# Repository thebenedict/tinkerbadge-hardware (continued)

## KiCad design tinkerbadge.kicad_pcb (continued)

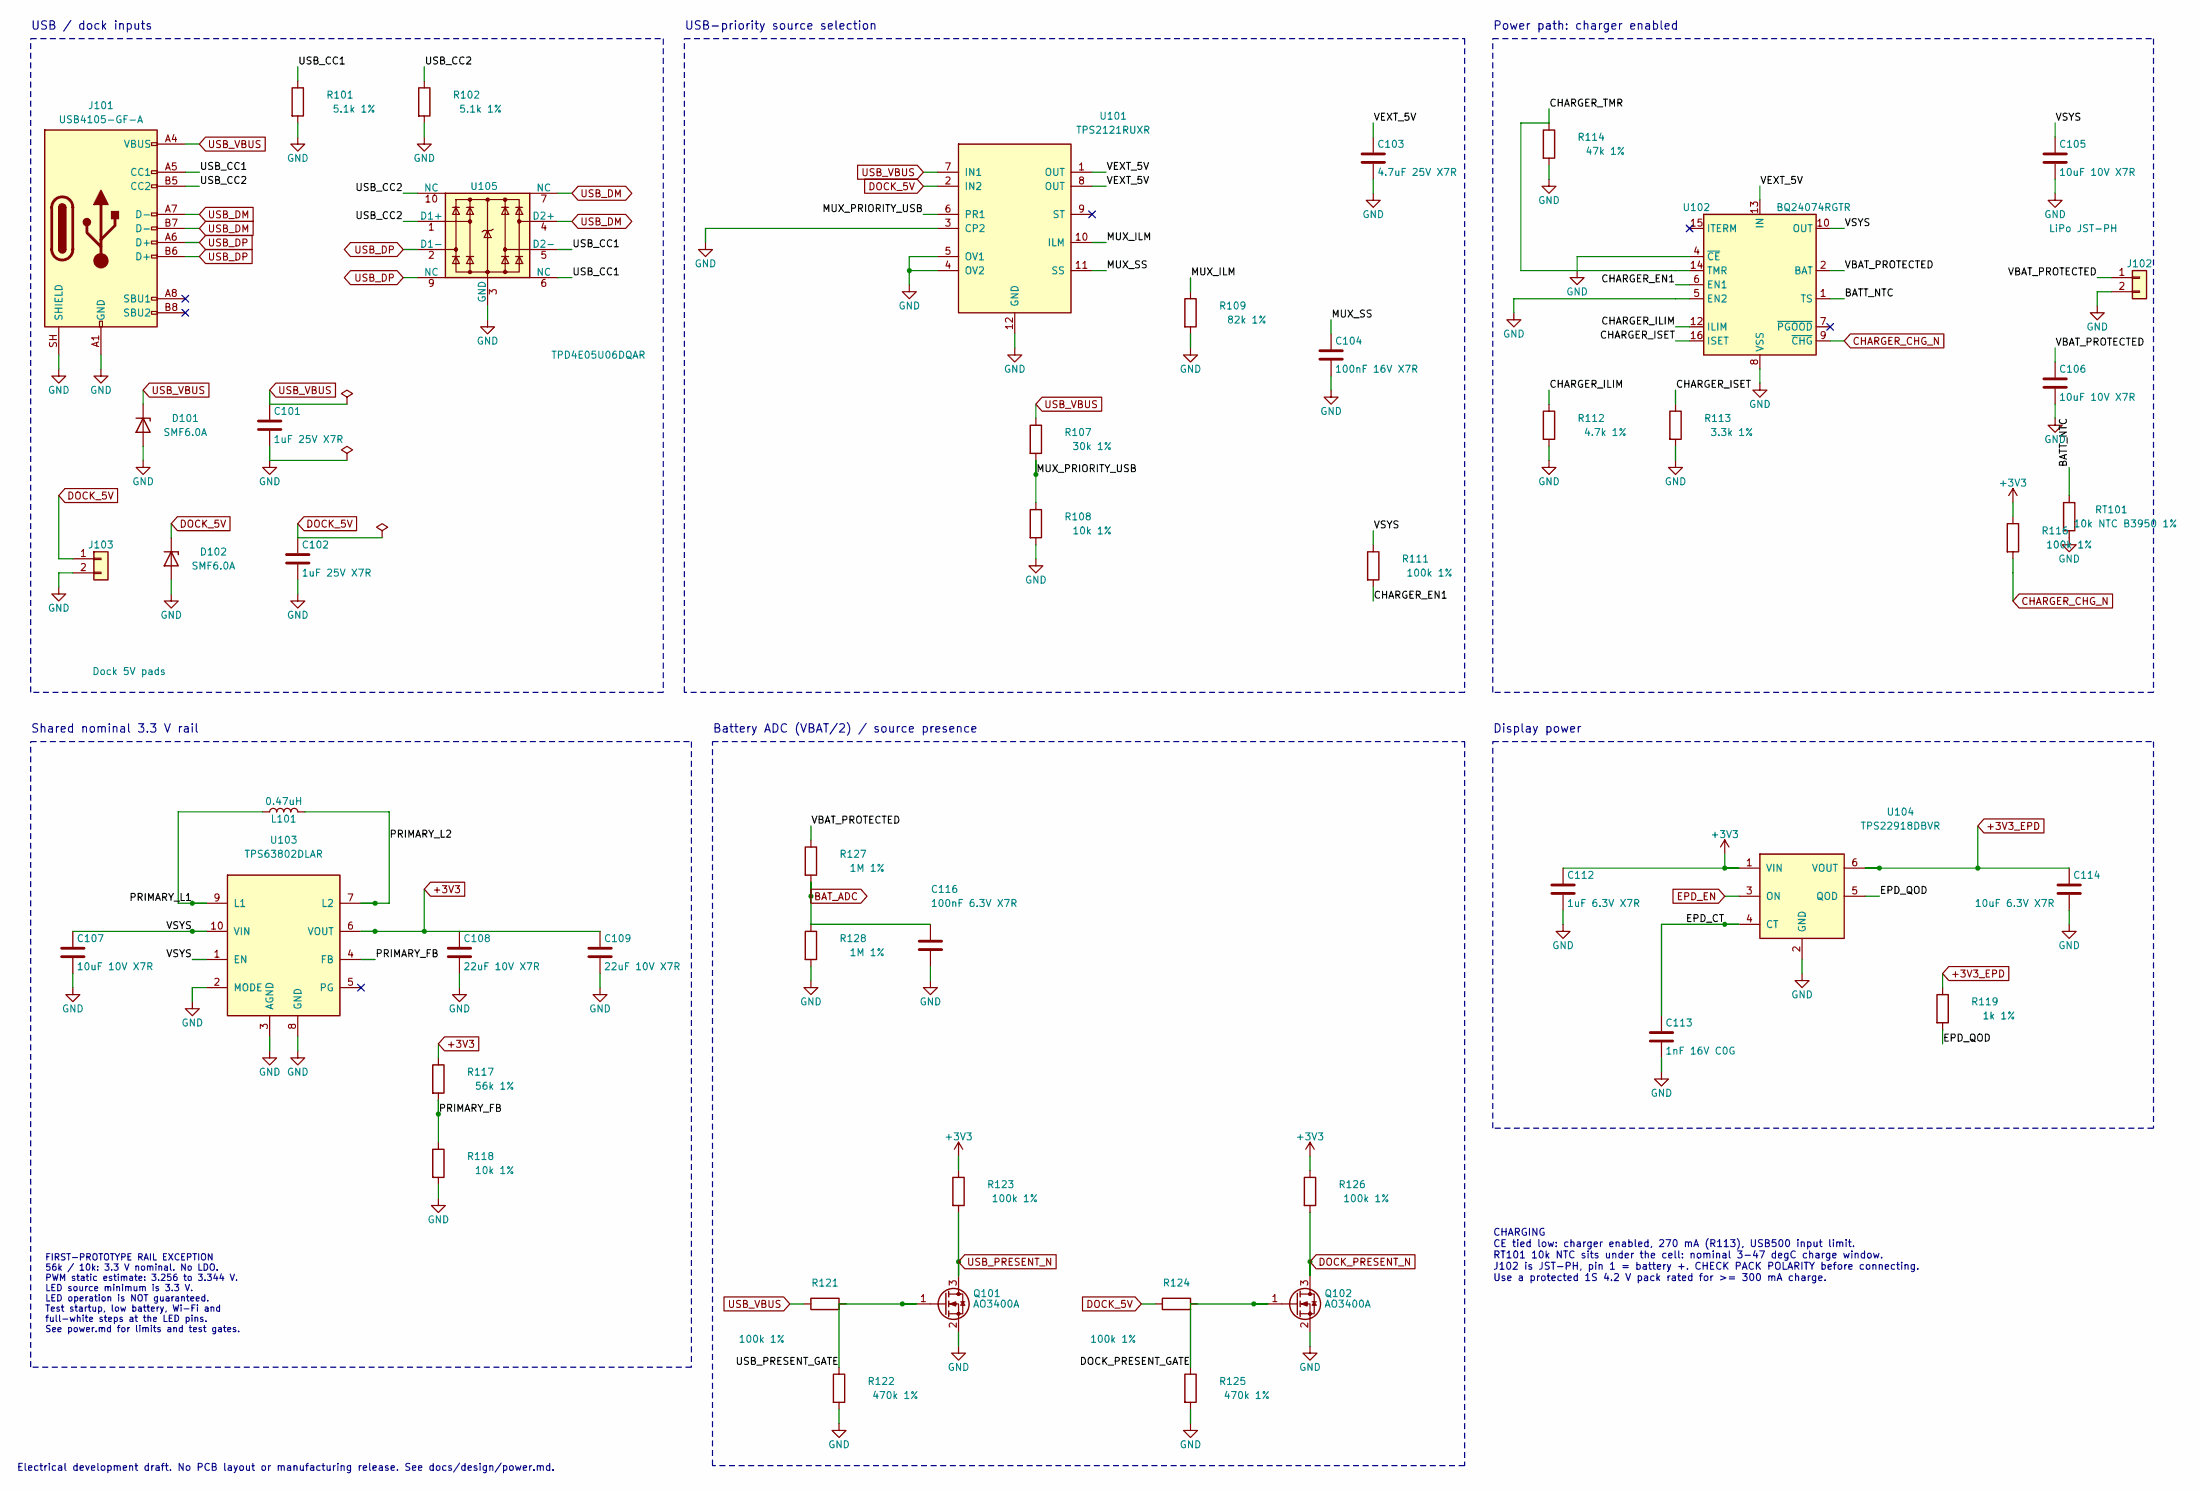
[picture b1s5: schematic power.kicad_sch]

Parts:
C101, C102: 1uF 25V X7R; C_0805_2012Metric; MPN CL21B105KBFNNNE; LCSC C28323
C103: 4.7uF 25V X7R; C_1206_3216Metric; MPN 1206B475K500NT; LCSC C29823
C104: 100nF 16V X7R; C_0603_1608Metric; MPN CC0603KRX7R9BB104; LCSC C14663
C105, C106, C107: 10uF 10V X7R; C_0805_2012Metric; MPN CL21A106KAYNNNE; LCSC C15850
C108, C109: 22uF 10V X7R; C_1210_3225Metric; MPN CL32B226KAJNNNE; LCSC C309062
C112: 1uF 6.3V X7R; C_0805_2012Metric; MPN CL21B105KBFNNNE; LCSC C28323
C113: 1nF 16V C0G; C_0603_1608Metric; MPN CL10B102KB8NNNC; LCSC C1588
C114: 10uF 6.3V X7R; C_0805_2012Metric; MPN CL21A106KAYNNNE; LCSC C15850
C116: 100nF 6.3V X7R; C_0603_1608Metric; MPN CC0603KRX7R9BB104; LCSC C14663
D101, D102: SMF6.0A; MPN SMF6.0A; LCSC C19077499
J101: USB4105-GF-A; USB4105-GF-A_ProjectShells; MPN USB4105-GF-A; LCSC C3020560
J102: LiPo JST-PH; JST_PH_S2B-PH-K_1x02_P2.00mm_Horizontal; MPN S2B-PH-K-S(LF)(SN); LCSC C173752
J103: Dock 5V pads; Dock_Pads_2x_4x6mm; MPN PCB pads only: no fitted component
L101: 0.47uH; L_Changjiang_FNR4020S; MPN SWPA4020SR47NT; LCSC C98415
Q101, Q102: AO3400A; SOT-23; MPN AO3400A; LCSC C20917
R101, R102: 5.1k 1%; R_0603_1608Metric; MPN 0603WAF5101T5E; LCSC C23186
R107: 30k 1%; R_0603_1608Metric; MPN 0603WAF3002T5E; LCSC C22984
R108, R118: 10k 1%; R_0603_1608Metric; MPN 0603WAF1002T5E; LCSC C25804
R109: 82k 1%; R_0603_1608Metric; MPN 0603WAF8202T5E; LCSC C23254
R111, R116, R121, R123, R124, R126: 100k 1%; R_0603_1608Metric; MPN 0603WAF1003T5E; LCSC C25803
R112: 4.7k 1%; R_0603_1608Metric; MPN 0603WAF4701T5E; LCSC C23162
R113: 3.3k 1%; R_0603_1608Metric; MPN 0603WAF3301T5E; LCSC C22978
R114: 47k 1%; R_0603_1608Metric; MPN 0603WAF4702T5E; LCSC C25819
R117: 56k 1%; R_0603_1608Metric; MPN 0603WAF5602T5E; LCSC C23206
R119: 1k 1%; R_0603_1608Metric; MPN 0603WAF1001T5E; LCSC C21190
R122, R125: 470k 1%; R_0603_1608Metric; MPN 0603WAF4703T5E; LCSC C23178
R127, R128: 1M 1%; R_0603_1608Metric; MPN 0603WAF1004T5E; LCSC C22935
RT101: 10k NTC B3950 1%; R_0603_1608Metric; MPN KNTC0603/10KF3950; LCSC C2892547
U101: TPS2121RUXR; TPS2121RUXR_Reviewed; MPN TPS2121RUXR; LCSC C485916
U102: BQ24074RGTR; BQ24074RGTR_Reviewed; MPN BQ24074RGTR; LCSC C54313
U103: TPS63802DLAR; TPS63802_DLA0010A_Reviewed; MPN TPS63802DLAR; LCSC C2845237
U104: TPS22918DBVR; SOT-23-6; MPN TPS22918DBVR; LCSC C131941
U105: TPD4E05U06DQAR; USON-10_2.5x1.0mm_P0.5mm; MPN TPD4E05U06DQAR; LCSC C138714

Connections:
+3V3: C108.1, C109.1, C112.1, R116.1, R117.1, R123.1, R126.1, U103.6 (VOUT), U104.1 (VIN); also elsewhere on the board
+3V3_EPD: C114.1, R119.1, U104.6 (VOUT); also elsewhere on the board
/01 POWER + CHARGING/BATT_NTC: RT101.1, U102.1 (TS)
/01 POWER + CHARGING/CHARGER_EN1: R111.2, U102.6 (EN1)
/01 POWER + CHARGING/CHARGER_ILIM: R112.1, U102.12 (ILIM)
/01 POWER + CHARGING/CHARGER_ISET: R113.1, U102.16 (ISET)
/01 POWER + CHARGING/DOCK_PRESENT_GATE: Q102.1 (G), R124.2, R125.1
/01 POWER + CHARGING/EPD_CT: C113.1, U104.4 (CT)
/01 POWER + CHARGING/EPD_QOD: R119.2, U104.5 (QOD)
/01 POWER + CHARGING/MUX_ILM: R109.1, U101.10 (ILM)
/01 POWER + CHARGING/MUX_PRIORITY_USB: R107.2, R108.1, U101.6 (PR1)
/01 POWER + CHARGING/MUX_SS: C104.1, U101.11 (SS)
/01 POWER + CHARGING/PRIMARY_FB: R117.2, R118.1, U103.4 (FB)
/01 POWER + CHARGING/PRIMARY_L1: L101.1, U103.9 (L1)
/01 POWER + CHARGING/PRIMARY_L2: L101.2, U103.7 (L2)
/01 POWER + CHARGING/USB_CC1: J101.A5 (CC1), R101.1, U105.5 (D2-), U105.6 (NC)
/01 POWER + CHARGING/USB_CC2: J101.B5 (CC2), R102.1, U105.1 (D1+), U105.10 (NC)
/01 POWER + CHARGING/USB_PRESENT_GATE: Q101.1 (G), R121.2, R122.1
/01 POWER + CHARGING/VBAT_PROTECTED: C106.1, J102.1, R127.1, U102.2 (BAT), U102.3 (BAT)
/01 POWER + CHARGING/VEXT_5V: C103.1, U101.1 (OUT), U101.8 (OUT), U102.13 (IN)
/01 POWER + CHARGING/VSYS: C105.1, C107.1, R111.1, U102.10 (OUT), U102.11 (OUT), U103.1 (EN), U103.10 (VIN)
BAT_ADC: C116.1, R127.2, R128.1; also elsewhere on the board
CHARGER_CHG_N: R116.2, U102.9 (~CHG); also elsewhere on the board
DOCK_PRESENT_N: Q102.3 (D), R126.2; also elsewhere on the board
EPD_EN: U104.3 (ON); also elsewhere on the board
USB_DM: J101.A7 (D-), J101.B7 (D-), U105.4 (D2+), U105.7 (NC); also elsewhere on the board
USB_DP: J101.A6 (D+), J101.B6 (D+), U105.2 (D1-), U105.9 (NC); also elsewhere on the board
USB_PRESENT_N: Q101.3 (D), R123.2; also elsewhere on the board

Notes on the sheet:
USB / dock inputs
USB-priority source selection
Power path: charger enabled
Battery ADC (VBAT/2) / source presence
Display power
Electrical development draft. No PCB layout or manufacturing release. See docs/design/power.md.
CHARGING CE tied low: charger enabled, 270 mA (R113), USB500 input limit. RT101 10k NTC sits under the cell: nominal 3-47 degC charge window. J102 is JST-PH, pin 1 = battery +. CHECK PACK POLARITY before connecting. Use a protected 1S 4.2 V pack rated for >= 300 mA charge.
Shared nominal 3.3 V rail
FIRST-PROTOTYPE RAIL EXCEPTION 56k / 10k: 3.3 V nominal. No LDO. PWM static estimate: 3.256 to 3.344 V. LED source minimum is 3.3 V. LED operation is NOT guaranteed. Test startup, low battery, Wi-Fi and full-white steps at the LED pins. See power.md for limits and test gates.

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
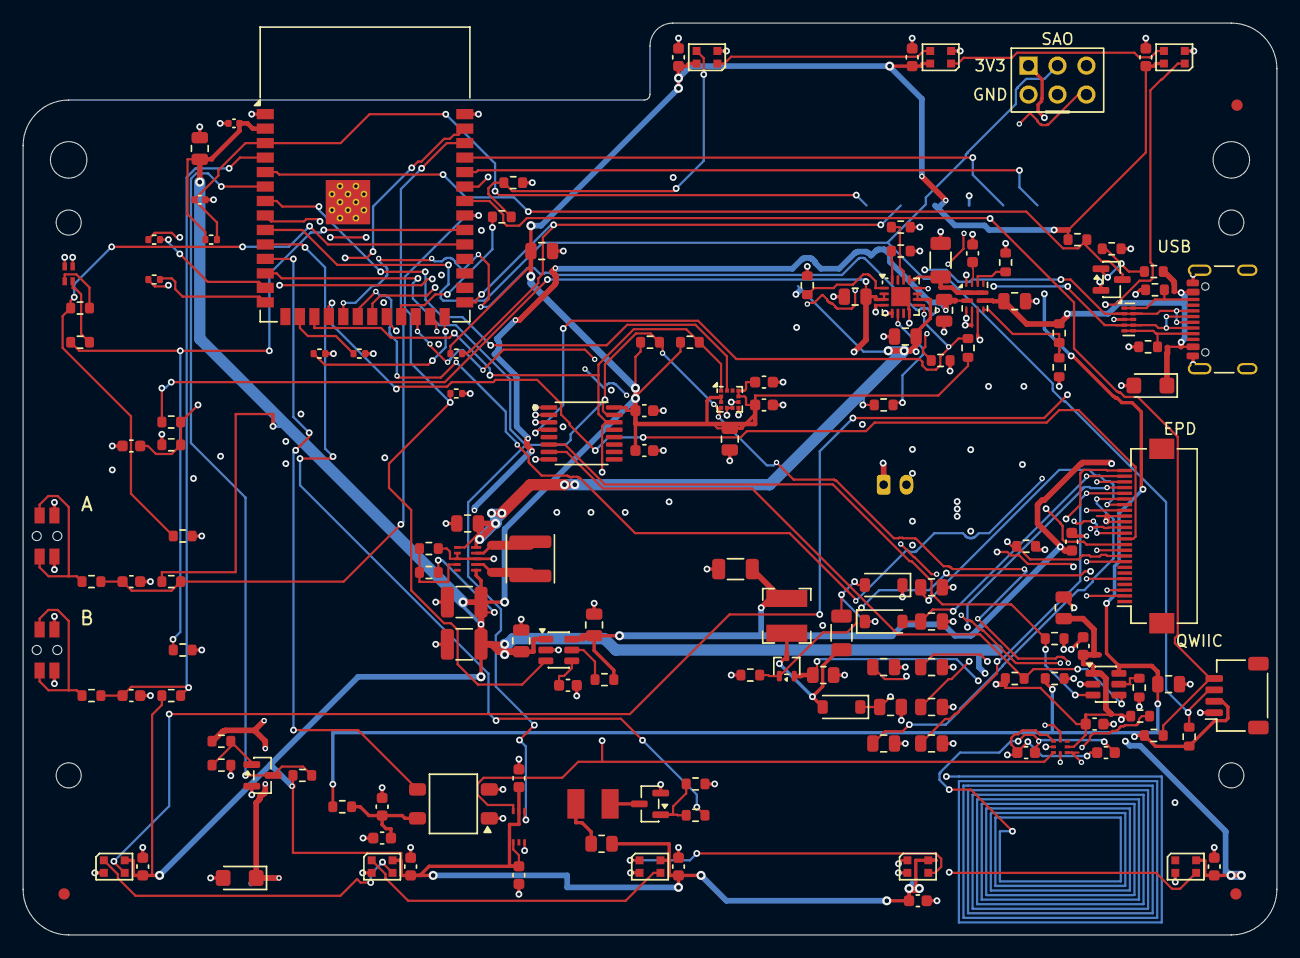
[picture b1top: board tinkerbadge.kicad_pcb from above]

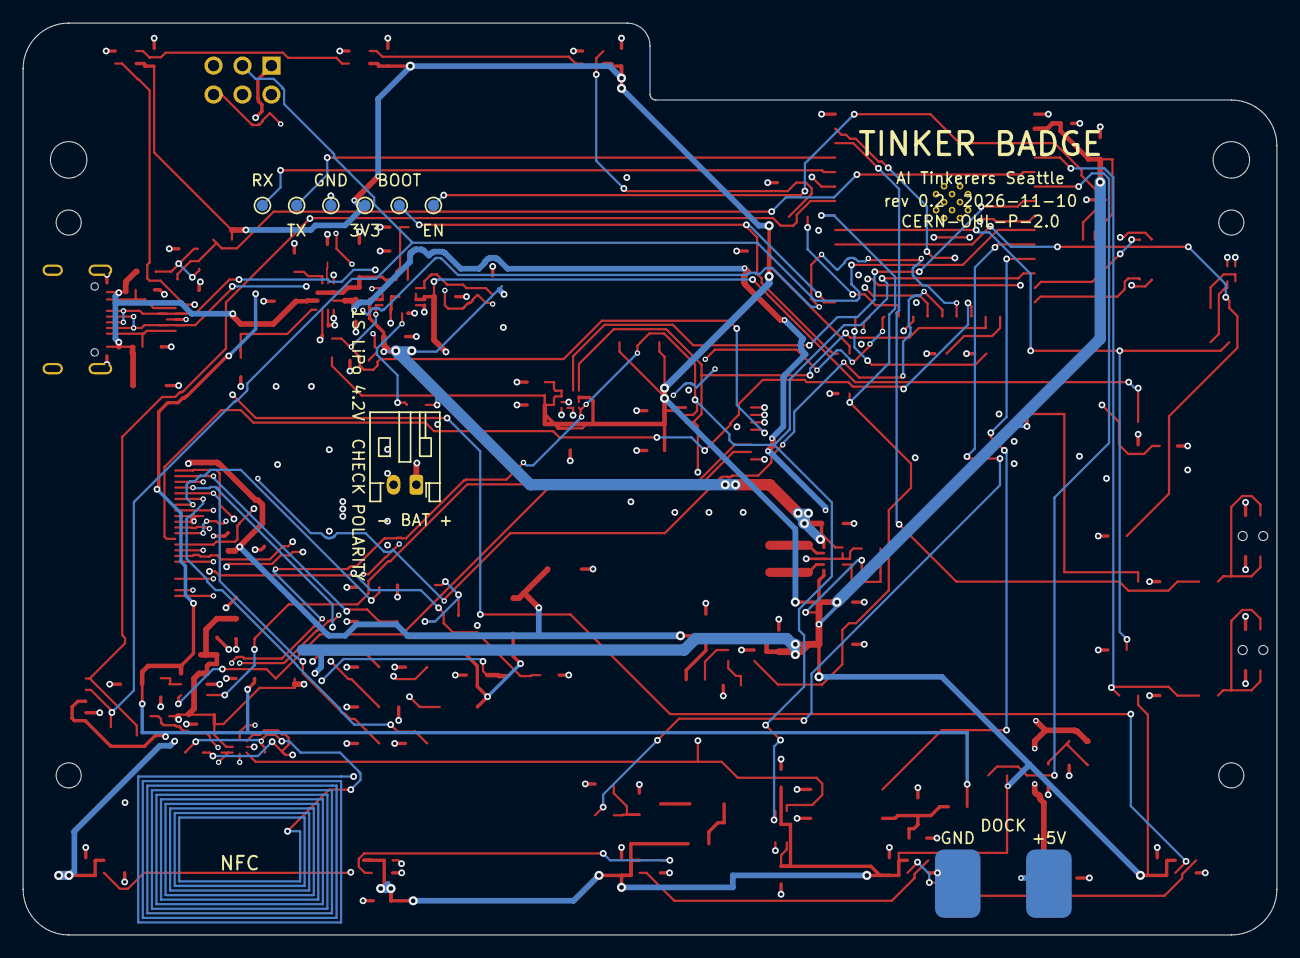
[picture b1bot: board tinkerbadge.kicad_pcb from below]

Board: 4 copper layers, 110.0 x 80.0 mm, 167 parts (10 on the bottom side), 95 nets.

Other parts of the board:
FID1, FID2, FID3: Fiducial; Fiducial_1mm_Mask2mm
H1, H2, H3, H4: PROVISIONAL; MountingHole_2.2mm_M2
H5, H6: REVIEW ENVELOPE ONLY; Review_Cord_Hole_3p2
MECH_BATTERY: REVIEW ONLY; Review_Battery_Allowance
MECH_PANEL: REVIEW ENVELOPE ONLY; Review_Panel_Raised_4p5

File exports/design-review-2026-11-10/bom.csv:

"Reference","Value","Footprint","MPN","Qty","DNP"
"C101,C102","1uF 25V X7R","Capacitor_SMD:C_0805_2012Metric","CL21B105KBFNNNE","2",""
"C103","4.7uF 25V X7R","Capacitor_SMD:C_1206_3216Metric","1206B475K500NT","1",""
"C104","100nF 16V X7R","Capacitor_SMD:C_0603_1608Metric","CC0603KRX7R9BB104","1",""
"C105-C107","10uF 10V X7R","Capacitor_SMD:C_0805_2012Metric","CL21A106KAYNNNE","3",""
"C108,C109","22uF 10V X7R","Capacitor_SMD:C_1210_3225Metric","CL32B226KAJNNNE","2",""
"C112","1uF 6.3V X7R","Capacitor_SMD:C_0805_2012Metric","CL21B105KBFNNNE","1",""
"C113","1nF 16V C0G","Capacitor_SMD:C_0603_1608Metric","CL10B102KB8NNNC","1",""
"C114","10uF 6.3V X7R","Capacitor_SMD:C_0805_2012Metric","CL21A106KAYNNNE","1",""
"C116","100nF 6.3V X7R","Capacitor_SMD:C_0603_1608Metric","CC0603KRX7R9BB104","1",""
"C201","22uF 10V X5R","Capacitor_SMD:C_0805_2012Metric","CL21A226MAQNNNE","1",""
"C202","100nF 16V X7R","Capacitor_SMD:C_0402_1005Metric","CL05B104KO5NNNC","1",""
"C203","1uF 10V X7R","Capacitor_SMD:C_0402_1005Metric","CL05A105KA5NQNC","1",""
"C301,C302","4.7u / 50V","Capacitor_SMD:C_1206_3216Metric","1206B475K500NT","2",""
"C303,C401-C408,C411,C412,C501-C504,C506,C510,C514","100n / 10V","Capacitor_SMD:C_0603_1608Metric","CC0603KRX7R9BB104","18",""
"C304","1u / 10V","Capacitor_SMD:C_0805_2012Metric","CL21B105KBFNNNE","1",""
"C305,C311","1u / 25V","Capacitor_SMD:C_0805_2012Metric","CL21B105KBFNNNE","2",""
"C306-C310","1u / 50V","Capacitor_SMD:C_0805_2012Metric","CL21B105KBFNNNE","5",""
"C409","22u / 10V","Capacitor_SMD:C_0805_2012Metric","CL21A226MAQNNNE","1",""
"C505,C512,C513","10u / 10V","Capacitor_SMD:C_0805_2012Metric","CL21A106KAYNNNE","3",""
"C507","27p C0G (tune)","Capacitor_SMD:C_0603_1608Metric","CC0603JRNPO9BN270","1",""
"C509","4.7u / 10V","Capacitor_SMD:C_0603_1608Metric","CL10A475KO8NNNC","1",""
"C511,C515","1u / 10V","Capacitor_SMD:C_0603_1608Metric","CL10A105KB8NNNC","2",""
"D101,D102","SMF6.0A","Tinkerbadge:SMF6.0A","SMF6.0A","2",""
"D301-D303","MBR0530T1G","Diode_SMD:D_SOD-123","MBR0530T1G","3",""
"D401-D408","WS2812C-2020-V6","Tinkerbadge:WS2812C-2020-V6_Reviewed","WS2812C-2020-V6","8",""
"D409","HSMF-C165","Tinkerbadge:HSMF-C165","HSMF-C165","1",""
"D501","IR67-21C/TR8","Tinkerbadge:IR67-21C_TR8","IR67-21C/TR8","1",""
"J101","USB4105-GF-A","Tinkerbadge:USB4105-GF-A_ProjectShells","USB4105-GF-A","1",""
"J102","LiPo JST-PH","Connector_JST:JST_PH_S2B-PH-K_1x02_P2.00mm_Horizontal","S2B-PH-K-S(LF)(SN)","1",""
"J301","ED037TC1_FPC","Connector_FFC-FPC:Hirose_FH12-24S-0.5SH_1x24-1MP_P0.50mm_Horizontal","FH12-24S-0.5SH(55)","1",""
"J501","SM04B-SRSS-TB(LF)(SN)","Tinkerbadge:JST_SH_SM04B_ProjectTabs","SM04B-SRSS-TB(LF)(SN)","1",""
"J502","SFH11-NBPC-D03-ST-BK","Tinkerbadge:SAO_Socket_2x03_Front","SFH11-NBPC-D03-ST-BK","1",""
"L101","0.47uH","Inductor_SMD:L_Changjiang_FNR4020S","SWPA4020SR47NT","1",""
"L301","68uH","Inductor_SMD:L_Bourns-SRN4018","SRN4018-680M","1",""
"Q101,Q102,Q501","AO3400A","Package_TO_SOT_SMD:SOT-23","AO3400A","3",""
"Q301","Si1308EDL-T1-GE3","Package_TO_SOT_SMD:SOT-323_SC-70","SI1308EDL-T1-GE3","1",""
"R101,R102","5.1k 1%","Resistor_SMD:R_0603_1608Metric","0603WAF5101T5E","2",""
"R107","30k 1%","Resistor_SMD:R_0603_1608Metric","0603WAF3002T5E","1",""
"R108,R118","10k 1%","Resistor_SMD:R_0603_1608Metric","0603WAF1002T5E","2",""
"R109","82k 1%","Resistor_SMD:R_0603_1608Metric","0603WAF8202T5E","1",""
"R111,R116,R121,R123,R124,R126","100k 1%","Resistor_SMD:R_0603_1608Metric","0603WAF1003T5E","6",""
"R112","4.7k 1%","Resistor_SMD:R_0603_1608Metric","0603WAF4701T5E","1",""
"R113","3.3k 1%","Resistor_SMD:R_0603_1608Metric","0603WAF3301T5E","1",""
"R114","47k 1%","Resistor_SMD:R_0603_1608Metric","0603WAF4702T5E","1",""
"R117","56k 1%","Resistor_SMD:R_0603_1608Metric","0603WAF5602T5E","1",""
"R119","1k 1%","Resistor_SMD:R_0603_1608Metric","0603WAF1001T5E","1",""
"R122,R125","470k 1%","Resistor_SMD:R_0603_1608Metric","0603WAF4703T5E","2",""
"R127,R128","1M 1%","Resistor_SMD:R_0603_1608Metric","0603WAF1004T5E","2",""
"R201-R204","10k 1%","Resistor_SMD:R_0402_1005Metric","0402WGF1002TCE","4",""
"R205,R206","22R 1%","Resistor_SMD:R_0402_1005Metric","0402WGF220JTCE","2",""
"R207","100k 1%","Resistor_SMD:R_0402_1005Metric","0402WGF1003TCE","1",""
"R301","0.47 / 0.25W","Resistor_SMD:R_0805_2012Metric","FBF05FT-R470-00L","1",""
"R302,R503","10k","Resistor_SMD:R_0603_1608Metric","0603WAF1002T5E","2",""
"R308,R402,R405,R406,R412,R414,R506,R509-R511","100k","Resistor_SMD:R_0603_1608Metric","0603WAF1003T5E","10",""
"R401,R411,R413","330","Resistor_SMD:R_0603_1608Metric","0603WAF3300T5E","3",""
"R403,R404","2.2k","Resistor_SMD:R_0603_1608Metric","0603WAF2201T5E","2",""
"R501,R502,R512,R513","4.7k","Resistor_SMD:R_0603_1608Metric","0603WAF4701T5E","4",""
"R504","100","Resistor_SMD:R_0805_2012Metric","0805W8F1000T5E","1",""
"R505,R507","100","Resistor_SMD:R_0603_1608Metric","0603WAF1000T5E","2",""
"R508","200k","Resistor_SMD:R_0603_1608Metric","0603WAF2003T5E","1",""
"RT101","10k NTC B3950 1%","Resistor_SMD:R_0603_1608Metric","KNTC0603/10KF3950","1",""
"SW401,SW402","SKSCLBE010","Tinkerbadge:SKSCLBE010","SKSCLBE010","2",""
"TP201","MCU_EN","TestPoint:TestPoint_Pad_D1.0mm","PCB pad only: no fitted component","1",""
"TP202","BOOT_N","TestPoint:TestPoint_Pad_D1.0mm","PCB pad only: no fitted component","1",""
"TP203","+3V3","TestPoint:TestPoint_Pad_D1.0mm","PCB pad only: no fitted component","1",""
"TP204","GND","TestPoint:TestPoint_Pad_D1.0mm","PCB pad only: no fitted component","1",""
"TP205","UART_TX","TestPoint:TestPoint_Pad_D1.0mm","PCB pad only: no fitted component","1",""
"TP206","UART_RX","TestPoint:TestPoint_Pad_D1.0mm","PCB pad only: no fitted component","1",""
"U101","TPS2121RUXR","Tinkerbadge:TPS2121RUXR_Reviewed","TPS2121RUXR","1",""
"U102","BQ24074RGTR","Tinkerbadge:BQ24074RGTR_Reviewed","BQ24074RGTR","1",""
"U103","TPS63802DLAR","Tinkerbadge:TPS63802_DLA0010A_Reviewed","TPS63802DLAR","1",""
"U104","TPS22918DBVR","Package_TO_SOT_SMD:SOT-23-6","TPS22918DBVR","1",""
"U105","TPD4E05U06DQAR","Package_SON:USON-10_2.5x1.0mm_P0.5mm","TPD4E05U06DQAR","1",""
"U201","ESP32-S3-WROOM-1-N16R8","RF_Module:ESP32-S3-WROOM-1","ESP32-S3-WROOM-1-N16R8","1",""
"U501","BH1730FVC","Tinkerbadge:BH1730FVC_WSOF6","BH1730FVC","1",""
"U502","LIS2DW12TR","Package_LGA:LGA-12_2x2mm_P0.5mm","LIS2DW12TR","1",""
"U503","NT3H2111W0FHKH","Tinkerbadge:NT3H2111W0FHKH_XQFN8","NT3H2111W0FHKH","1",""
"U504","IRM-H638T/TR2","Tinkerbadge:IRM-H638T_Reviewed","IRM-H638T/TR2","1",""
"U505","TPS2553DBVR","Package_TO_SOT_SMD:SOT-23-6","TPS2553DBVR","1",""
"U506","TCA9534PWR","Package_SO:TSSOP-16_4.4x5mm_P0.65mm","TCA9534PWR","1",""

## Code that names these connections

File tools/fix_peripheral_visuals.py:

#!/usr/bin/env python3
"""Targeted visual fixes after saved-sheet render review; native writes via MCP."""
import json,pathlib,time
from konnect_call import Client,unbox
root=pathlib.Path(__file__).resolve().parents[1];out=root/'.build/peripheral_cad';calls=[]
def add(sheet,name,**a):calls.append(dict(name=name,arguments=dict(schematic=str(root/(sheet+'.kicad_sch')),**a)))
def fields(sheet,r,x,y,rot=0):add(sheet,'edit_schematic_component',reference=r,field_placements={'Reference':dict(x=x,y=y,rotation=rot),'Value':dict(x=x,y=y+2.54,rotation=rot)})
def oldwire(sheet,a,b):add(sheet,'delete_schematic_wire',x1=a[0],y1=a[1],x2=b[0],y2=b[1])
def wires(sheet,points):add(sheet,'batch_add_wire',wires=[dict(x1=a[0],y1=a[1],x2=b[0],y2=b[1]) for a,b in zip(points,points[1:])])
def label(sheet,n,x,y,g=False,rot=0):add(sheet,'add_schematic_net_label',net=n,x=x,y=y,label_type='global_label' if g else 'net_label',rotation=rot,shape='bidirectional')
def dellabel(sheet,n,x,y):add(sheet,'delete_schematic_net_label',net=n,x=x,y=y)
for r,x in [('SW401',195.58),('SW402',297.18)]:fields('lighting',r,x,207.01,0)
for n,x,y,rot in [('VLED_3V9',25.4,55.88,180),('PWR_LED_G',35.56,179.07,180),('PWR_LED_R',35.56,184.15,180),('BTN_A_N',269.24,177.8,0),('BTN_B_N',370.84,177.8,0)]:add('lighting','rotate_schematic_label',net=n,x=x,y=y,rotation=rot)
dellabel('lighting','RGB_DIN',48.26,88.9);label('lighting','RGB_DIN',44.45,88.9)
fields('peripherals','U502',175.26,22.86);fields('peripherals','U506',76.2,127);fields('peripherals','C512',251.46,140.97)
for n,x,y in [('I2C_SDA',22.86,78.74),('I2C_SCL',38.1,73.66),('+3V3',147.32,86.36)]:add('peripherals','rotate_schematic_label',net=n,x=x,y=y,rotation=180)
# Longer local enable stub clears the neighboring charge-status global label.
dellabel('peripherals','ACC_EN',91.44,167.64);wires('peripherals',[(91.44,167.64),(116.84,167.64)]);label('peripherals','ACC_EN',116.84,167.64)
# Move the lower fault return away from the output capacitor's ground legend.
dellabel('peripherals','ACC_FAULT_N',314.96,203.2)
for a,b in [((304.8,177.8),(304.8,203.2)),((304.8,203.2),(368.3,203.2)),((368.3,203.2),(368.3,187.96))]:oldwire('peripherals',a,b)
wires('peripherals',[(304.8,177.8),(304.8,209.55),(368.3,209.55),(368.3,187.96)]);label('peripherals','ACC_FAULT_N',314.96,209.55)
dellabel('peripherals','IR_GATE',45.72,255.27);label('peripherals','IR_GATE',39.37,255.27)
# Route receiver output below its decoupling ground symbol.
dellabel('peripherals','IR_RX_N',181.61,251.46);oldwire('peripherals',(176.53,251.46),(181.61,251.46));wires('peripherals',[(176.53,251.46),(177.8,251.46),(177.8,260.35),(182.88,260.35)]);label('peripherals','IR_RX_N',182.88,260.35,True)
# Place the IR TX supply after the expander note, without a wire through its text.
oldwire('peripherals',(58.42,218.44),(58.42,213.36));oldwire('peripherals',(58.42,226.06),(58.42,233.68))
add('peripherals','move_schematic_component',reference='R504',x=58.42,y=224.79);add('peripherals','move_schematic_component',reference='#PWR028',x=58.42,y=220.98)
wires('peripherals',[(58.42,228.6),(58.42,233.68)]);fields('peripherals','R504',62.23,223.52)
# Clear Qwiic power text from the adjacent ground marker.
dellabel('peripherals','ACC_3V3',269.24,240.03);wires('peripherals',[(269.24,240.03),(254,240.03)]);label('peripherals','ACC_3V3',254,240.03,False,180)
(out/'visual_fix_plan.json').write_text(json.dumps(calls,indent=2));cli=Client()
try:
 for i,c in enumerate(calls):
  r=cli.call(c['name'],c['arguments']);(out/f'visual-fix-{i:03d}-{c["name"]}.json').write_text(json.dumps(r,indent=2));u=unbox(r);v=u['result'][0]
  if u['isError'] or isinstance(v,dict) and (v.get('errors') or v.get('failures') or v.get('success') is False):raise RuntimeError(str(u))
 for sh in ['lighting','peripherals']:
  r=cli.call('render_schematic_png',dict(schematic=str(root/(sh+'.kicad_sch')),output=str(out/(sh+'.png')),width_px=4096));(out/(sh+'_render_final.json')).write_text(json.dumps(r,indent=2));print(unbox(r))
finally:cli.close()

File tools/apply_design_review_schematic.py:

#!/usr/bin/env python3
"""Apply the 2026-11-10 design-review schematic changes (docs/design/design_review_2026-11-10.md).

One-shot, non-idempotent edit of the native sheets. Run from the repository
root on a clean checkout of the pre-review schematic, then normalise with
`kicad-cli sch upgrade --force tinkerbadge.kicad_sch`.
"""
import pathlib
import sys

sys.path.insert(0, str(pathlib.Path(__file__).parent))
from schlib import Sheet, kid, kids, pt, prop, pval, parse  # noqa: E402

pwr_n = [900]


def gnd(sheet, at, template=None):
    """Clone a GND power symbol so that its pin lands on `at`."""
    if template is None:
        template = next(pval(s, 'Reference') for s in sheet.symbols()
                        if pval(s, 'Reference').startswith('#') and pval(s, 'Value') == 'GND'
                        and float(kid(s, 'at')[3]) == 0 and kid(s, 'mirror') is None)
    pwr_n[0] += 1
    sheet.clone_symbol(template, f'#PWR{pwr_n[0]}', at)


def drop_stub(sheet, pin_pt):
    ws, pts = sheet.trace(pin_pt)
    sheet.remove(ws + sheet.items_at(pts))


def set_fp(sheet, ref, fp, mpn=None, value=None):
    sheet.set_prop(ref, 'Footprint', fp)
    if mpn:
        sheet.set_prop(ref, 'MPN', mpn)
    if value:
        sheet.set_prop(ref, 'Value', value)


def set_dnp(sheet, ref, state=True):
    s = sheet.by_ref(ref)
    kid(s, 'dnp')[1] = type(kid(s, 'dnp')[1])('yes' if state else 'no')
    kid(s, 'in_bom')[1] = type(kid(s, 'in_bom')[1])('no' if state else 'yes')


# ---------------------------------------------------------------- power
p = Sheet('power.kicad_sch')

# 1. Battery ADC: plain 1M/1M divider with 100 nF, no analog switch.
for ref in ('U107', 'C115', 'R129', 'R130'):
    p.remove_symbol(ref)
for n in list(kids(p.root, 'label')):
    if n[1] == 'BAT_DIV_PRE':
        at = kid(n, 'at')
        p.remove([n])
        p.add_label('BAT_ADC', (float(at[1]), float(at[2])), 0, kind='global', shape='output')
p.set_prop('R127', 'Value', '1M 1%')
p.set_prop('R128', 'Value', '1M 1%')
p.set_prop('C116', 'Value', '100nF 6.3V X7R')

# 2. Charger input mode fixed at USB500: EN1 pulled high, EN2 low.
for ref in ('Q103', 'R110'):
    p.remove_symbol(ref)
u101 = p.pins(p.by_ref('U101'))
drop_stub(p, u101['9'])
p.add_nc(u101['9'])

# 3. Mux over-voltage supervisors unused (charger tolerates 28 V, OVP 10.5 V).
for ref in ('R103', 'R104', 'R105', 'R106'):
    p.remove_symbol(ref)
for pin in ('5', '4'):
    drop_stub(p, u101[pin])
x = 176.53
p.add_wire(u101['5'], (x, u101['5'][1]))
p.add_wire(u101['4'], (x, u101['4'][1]))
p.add_wire((x, u101['5'][1]), (x, u101['4'][1]))
p.add_wire((x, u101['4'][1]), (x, 66.04))
p.add_junction((x, u101['4'][1]))
gnd(p, (x, 66.04))

# 4. Charging enabled in hardware: CE tied low.
u102 = p.pins(p.by_ref('U102'))
p.remove_symbol('R120')
ce = u102['4']
p.add_wire(ce, (297.18, ce[1]))
p.add_wire((297.18, ce[1]), (297.18, 63.5))
gnd(p, (297.18, 63.5))

# 5. On-board cell-area NTC replaces the DNP thermistor connector.
j104 = p.pins(p.by_ref('J104'))
p.remove_symbol('J104')
for n in kids(p.root, 'label'):
    if n[1] == 'BATT_NTC_OPTIONAL':
        n[1] = 'BATT_NTC'
rt = p.clone_symbol('R113', 'RT101', (386.08, 107.95), 0, '10k NTC B3950 1%')
rtp = p.pins(rt)
p.add_wire(rtp['1'], (rtp['1'][0], 99.06))
p.add_label('BATT_NTC', (rtp['1'][0], 99.06), 90)
gnd(p, rtp['2'])
set_fp(p, 'RT101', 'Resistor_SMD:R_0603_1608Metric', 'NTC 10k B25/50=3950 1% 0603 (select at quote)')
p.set_prop('RT101', 'Description', 'NTC thermistor under the cell; BQ24074 TS charge-temperature window')

# 5b. Charger PGOOD is redundant with USB/dock presence sensing: leave it unconnected.
p.remove_symbol('R115')
drop_stub(p, u102['7'])
p.add_nc(u102['7'])

# 5c. USB ESD array: map channels in connector order (CC2, D+, D-, CC1) and tie
# each NC twin pad to its line so the traces run straight through the package.
u105 = p.pins(p.by_ref('U105'))
for pin in ('1', '2', '4', '5'):
    drop_stub(p, u105[pin])
p.remove([n for n in kids(p.root, 'no_connect') if pt(kid(n, 'at')) in {u105[k] for k in ('6', '7', '9', '10')}])
for pins, net, kind in ((('1', '10'), 'USB_CC2', 'label'), (('2', '9'), 'USB_DP', 'global'),
                        (('4', '7'), 'USB_DM', 'global'), (('5', '6'), 'USB_CC1', 'label')):
    for pin in pins:
        x, y = u105[pin]
        left = x < 100.33
        end = (x - 2.54, y) if left else (x + 2.54, y)
        p.add_wire((x, y), end)
        p.add_label(net, end, 180 if left else 0, kind=kind, shape='bidirectional')

# 6. E24 / 1 % value consolidation.
for ref, val in {'R107': '30k 1%', 'R108': '10k 1%', 'R109': '82k 1%', 'R112': '4.3k 1%',
                 'R113': '3.3k 1%', 'R114': '47k 1%', 'R117': '56k 1%', 'R118': '10k 1%'}.items():
    p.set_prop(ref, 'Value', val)

# 7. Footprints for previously blank parts.
set_fp(p, 'U105', 'Package_SON:USON-10_2.5x1.0mm_P0.5mm')
set_fp(p, 'J102', 'Connector_JST:JST_PH_S2B-PH-K_1x02_P2.00mm_Horizontal', 'S2B-PH-K-S(LF)(SN)', 'LiPo JST-PH')
set_fp(p, 'J103', 'Tinkerbadge:Dock_Pads_2x_4x6mm', 'PCB pads only: no fitted component', 'Dock 5V pads')
kid(p.by_ref('J103'), 'in_bom')[1] = type(kid(p.by_ref('J103'), 'in_bom')[1])('no')
set_fp(p, 'L101', 'Inductor_SMD:L_Coilcraft_XxL4020', 'XFL4015-471MEB')

# Sheet notes that described the removed circuits.
for t in kids(p.root, 'text'):
    s = t[1]
    if 'R120 fitted' in s:
        t[1] = ('CHARGING\\nCE tied low: charger enabled, 270 mA (R113), USB500 input limit.\\n'
                'RT101 10k NTC sits under the cell: nominal 3-47 degC charge window.\\n'
                'J102 is JST-PH, pin 1 = battery +. CHECK PACK POLARITY before connecting.\\n'
                'Use a protected 1S 4.2 V pack rated for >= 300 mA charge.').replace('\\n', '\n')
    elif 'charging disabled' in s:
        t[1] = s.replace('charging disabled', 'charger enabled')
    elif 'Battery ADC' in s:
        t[1] = 'Battery ADC (VBAT/2) / source presence'
p.save()

# -------------------------------------------------------------- display
d = Sheet('display.kicad_sch')
j301 = d.pins(d.by_ref('J301'))
for ref in ('U301', 'C312', 'R303', 'R304', 'R305', 'R306', 'R307'):
    d.remove_symbol(ref)
for pin, net in {'14': 'EPD_MOSI', '13': 'EPD_SCK', '12': 'EPD_CS_N', '11': 'EPD_DC', '10': 'EPD_RST_N'}.items():
    x, y = j301[pin]
    d.add_wire((x, y), (x - 5.08, y))
    d.add_label(net, (x - 5.08, y), 180, kind='global', shape='input')
set_fp(d, 'J301', 'Connector_FFC-FPC:Hirose_FH12-24S-0.5SH_1x24-1MP_P0.50mm_Horizontal', 'FH12-24S-0.5SH(55)')
set_fp(d, 'L301', 'Inductor_SMD:L_Bourns-SRN4018', 'SRN4018-680M')
for t in kids(d.root, 'text'):
    s = t[1]
    if s.startswith('U301 isolates'):
        t[1] = 'MCU drives the panel directly. Firmware must drive SPI/DC/RST low before EPD_EN goes low.'
    elif 'J301 intentionally has no PCB footprint' in s:
        t[1] = 'J301: FH12 bottom-contact footprint. VERIFY flex pin-1 side on a real panel before fab.'
    elif s.startswith('Boot / off-state bias'):
        t[1] = 'BUSY bias'
d.save()

# ---------------------------------------------------------- peripherals
q = Sheet('peripherals.kicad_sch')
u506 = q.pins(q.by_ref('U506'))
for ref in ('R514', 'R515', 'R516', 'R517'):
    q.remove_symbol(ref)          # unused expander pins: firmware drives them low
for pin in ('5', '9', '10', '11', '12'):
    drop_stub(q, u506[pin])
    q.add_nc(u506[pin])
q.set_prop('R508', 'Value', '200k')
for t in kids(q.root, 'text'):
    if t[1].startswith('50 mA normal total'):
        t[1] = '50 mA normal total. 200k / 1% sets roughly 115-160 mA current limit.'
set_fp(q, 'J502', 'Tinkerbadge:SAO_Socket_2x03_Front', 'SFH11-NBPC-D03-ST-BK')
set_fp(q, 'AE501', 'Tinkerbadge:NFC_Coil_Rear_18x13', 'PCB feature: no fitted component', 'NFC PCB coil')
set_dnp(q, 'C508')
q.set_prop('C507', 'Value', '27p C0G (tune)')
q.set_prop('C507', 'Rating', '27p C0G 50V')
q.set_prop('C507', 'Population', 'fitted')
q.set_prop('R508', 'Rating', '200k 1%')
kid(q.by_ref('AE501'), 'in_bom')[1] = type(kid(q.by_ref('AE501'), 'in_bom')[1])('no')
q.save()
print('schematic changes applied')

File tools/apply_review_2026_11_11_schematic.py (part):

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for t in kids(light.root, 'text'):
    if 'BTN_B' in t[1] or 'Button B' in t[1]:
        pass
text(light, 'BTN_B_N is GPIO0: holding B through a reset enters ROM download. Pull-up R202 is on the processor sheet.', (292.1, 200.66))

# ---------------------------------------------------------------- mcu: GPIO0 / GPIO4 / reset
u201 = mcu.pins(mcu.by_ref('U201'))
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        at = kid(n, 'at')
        rot = int(float(at[3])) if len(at) > 3 else 0
        mcu.remove([n])
        mcu.add_label('BTN_B_N', (float(at[1]), float(at[2])), rot, kind='global', shape='input')
mcu.set_prop('TP202', 'Value', 'BOOT / BTN_B')
for t in kids(mcu.root, 'text'):
    if t[1].startswith('Hold BOOT low'):
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mcu.add_wire(swp['4'], (swp['4'][0], 180.34))
gnd(mcu, (swp['4'][0], 180.34))
mcu.add_wire(rp['2'], (rp['2'][0] + 2.54, rp['2'][1]))
mcu.add_label('MCU_EN', (rp['2'][0] + 2.54, rp['2'][1]), 0)
mcu.add_label('MCU_EN_SW', (swp['1'][0] + 1.27, swp['1'][1]), 0)
text(mcu, 'RESET (recessed): SW403 pulls EN low through 330R.', (93.98, 165.1))

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rt2 = power.clone_symbol('RT101', 'RT102', (x1 + 12.7, float(kid(rt1, 'at')[2])), 0, '100k NTC B3950 1%')
p2 = power.pins(rt2)
power.add_wire(p2['1'], (p2['1'][0], 99.06))
power.add_label('BATT_NTC', (p2['1'][0], 99.06), 90)
gnd(power, p2['2'])
for k, v in {'MPN': 'KNTC0603/100KF3950', 'LCSC': 'C2892545',
             'Description': 'Second NTC in parallel with RT101; shifts the BQ24074 TS window about 2.4 degC colder'}.items():
    power.set_prop('RT102', k, v)
testpoint(power, mcu, 'TP101', (345.44, 33.02), 'VSYS', 'label', 'docs/design/power_contract.json')
for t in kids(power.root, 'text'):
    if t[1].startswith('CHARGING'):
        t[1] = ('CHARGING\nCE tied low: charger enabled, 270 mA (R113), USB500 input limit.\n'
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                       'footprint': 'TestPoint:TestPoint_Pad_D1.0mm'}

m = load('mcu')
get(m, 'U201')['pins'].update({'4': None, '27': 'BTN_B_N'})
get(m, 'R202')['pins']['2'] = 'BTN_B_N'
tp = get(m, 'TP202'); tp['pins']['1'] = 'BTN_B_N'; tp['value'] = 'BOOT / BTN_B'
m['components'].append({'ref': 'SW403', 'mpn': 'SKSCLBE010', 'lib_id': 'Tinkerbadge_Peripherals:SKSCLBE010',
                        'pins': {'1': 'MCU_EN_SW', '2': 'MCU_EN_SW', '3': 'GND', '4': 'GND'},
                        'footprint': 'Tinkerbadge:SKSCLBE010', 'note': 'Recessed reset button. ' + NOTE})
m['components'].append({'ref': 'R415', 'lib_id': 'Device:R', 'pins': {'1': 'MCU_EN_SW', '2': 'MCU_EN'},
                        'footprint': 'Resistor_SMD:R_0603_1608Metric',
                        'note': '330R limits the C203 discharge current through the switch contact; EN low level about 0.1 V.'})
m['gpio']['0'] = 'BTN_B_N'
m['gpio']['4'] = 'NC'
m['unused_pins']['U201'] = sorted(set(m['unused_pins']['U201']) | {'4'}, key=int)
m['notes'] = [n.replace('GPIO0 BOOT10k pullup', 'GPIO0 is BOOT and button B with a 10k pullup (R202) and 100 nF (C412)') for n in m['notes']]
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
w = load('power')
w['two_terminal_support'].append({
    'ref': 'RT102', 'kind': 'R', 'value': '100k NTC B3950 1%', 'pins': {'1': 'BATT_NTC', '2': 'GND'}, 'fitted': True,
    'note': 'In parallel with RT101. Charge window 1.7-44.8 degC nominal, 0.1-48.4 degC over BQ24074 threshold/bias tolerance. ' + NOTE,
    'footprint': 'Resistor_SMD:R_0603_1608Metric',
    'footprint_status': 'standard KiCad library footprint; verify against the exact part drawing before fabrication'})
w['components'].append({'ref': 'TP101', 'mpn': None, 'facts': None, 'status': 'rear probe pad', 'pins': {'1': 'VSYS'},
                        'footprint': 'TestPoint:TestPoint_Pad_D1.0mm'})
save('power', w)

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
